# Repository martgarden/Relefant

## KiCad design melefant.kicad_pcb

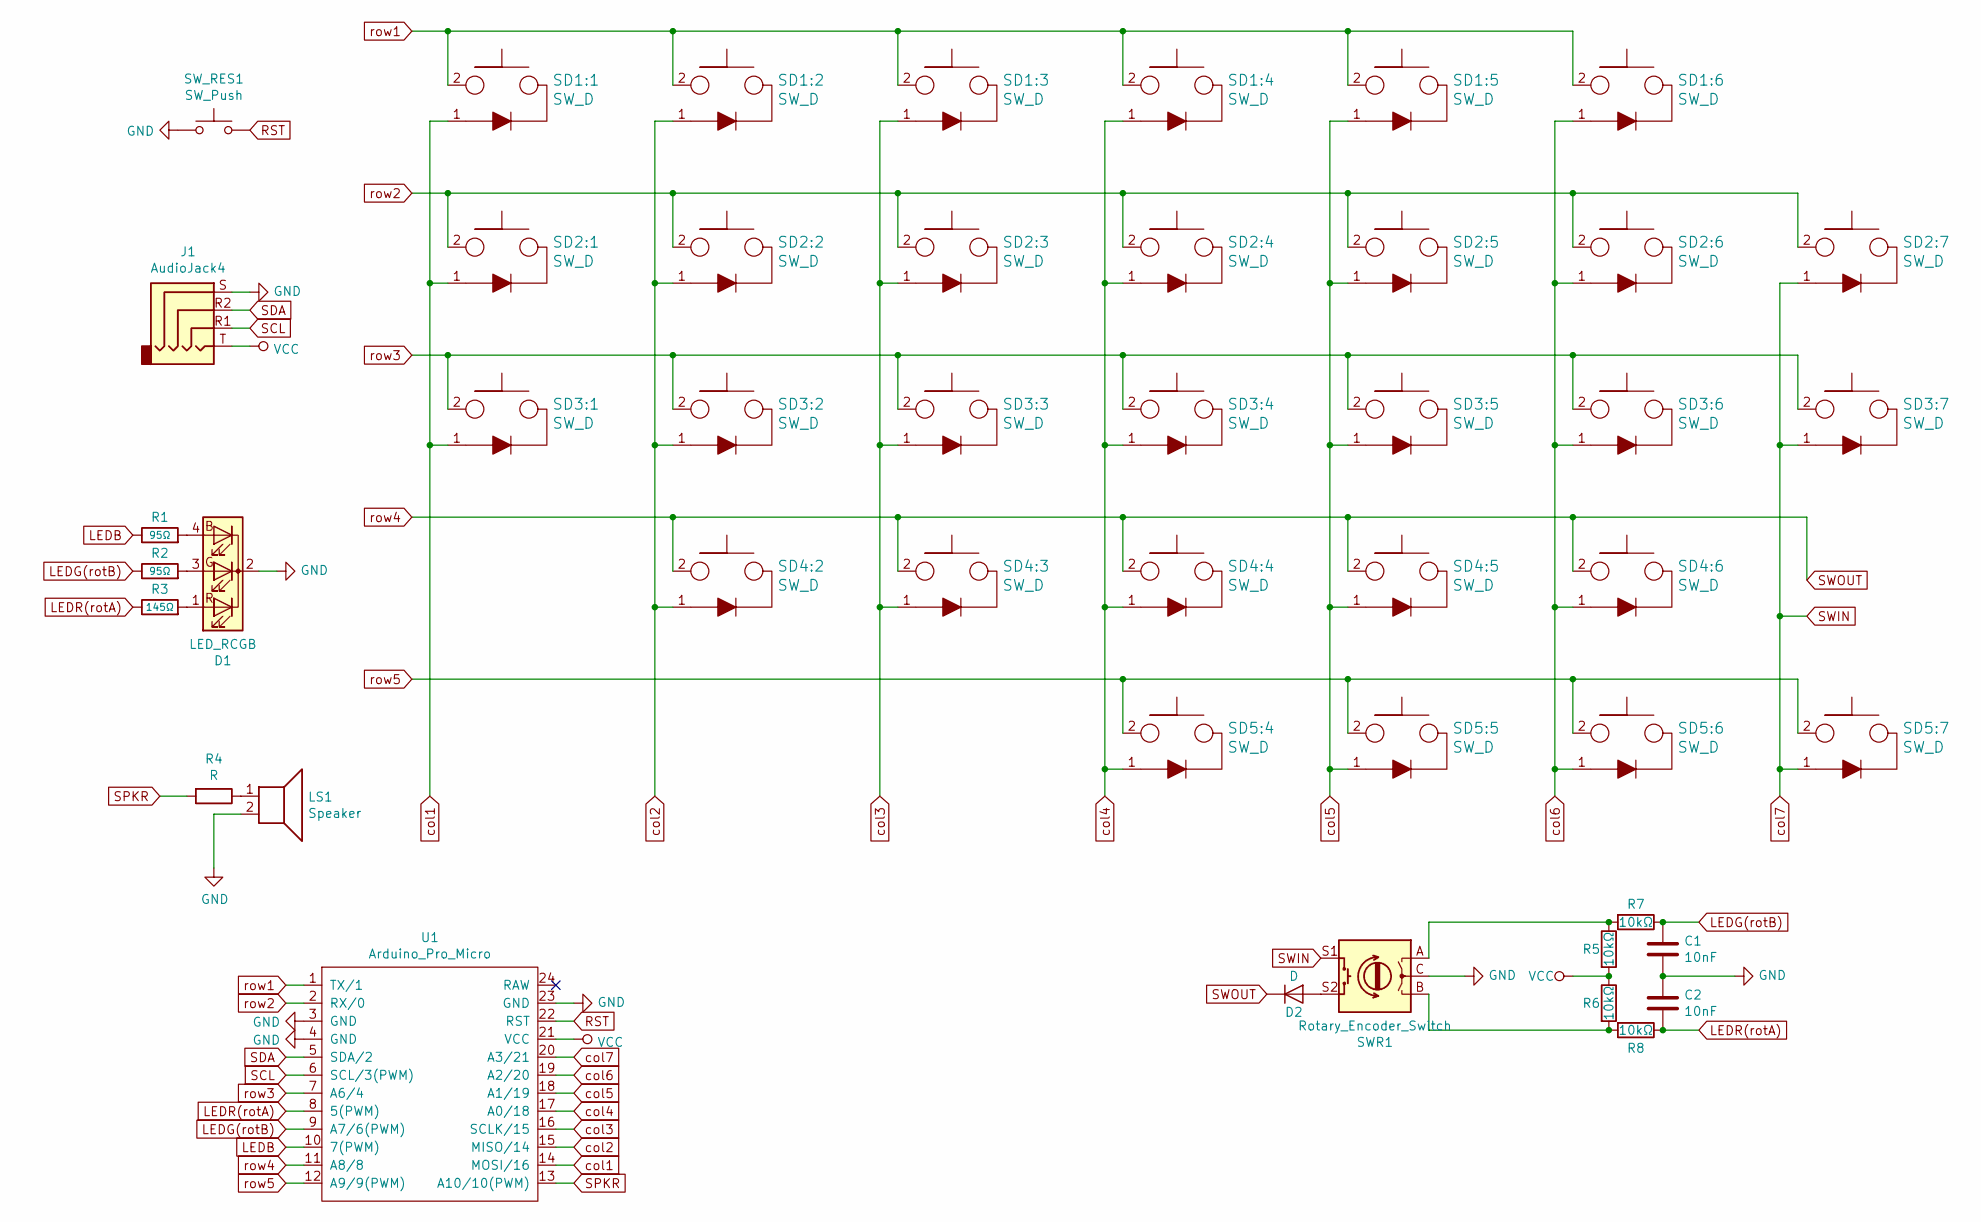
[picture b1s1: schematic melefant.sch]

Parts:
C1, C2: 10nF; C_Disc_D3.0mm_W2.0mm_P2.50mm
D1: LED_RCGB; LED_D5.0mm-4_RGB
D2: D; D_SOD123
J1: AudioJack4; TRRS-PJ320A-dbl
LS1: Speaker; PinHeader_1x02_P2.00mm_Vertical
R1, R2: 95Ω; R_Axial_DIN0207_L6.3mm_D2.5mm_P10.16mm_Horizontal
R3: 145Ω; R_Axial_DIN0207_L6.3mm_D2.5mm_P10.16mm_Horizontal
R4: R; R_Axial_DIN0207_L6.3mm_D2.5mm_P10.16mm_Horizontal
R5, R6, R7, R8: 10kΩ; R_Axial_DIN0207_L6.3mm_D2.5mm_P10.16mm_Horizontal
SD1:1, SD1:2, SD1:3, SD1:4, SD1:5, SD1:6, SD2:1, SD2:2, SD2:3, SD2:4, SD2:5, SD2:6, SD2:7, SD3:1, SD3:2, SD3:3, SD3:4, SD3:5, SD3:6, SD3:7, SD4:2, SD4:3, SD4:4, SD4:5, SD4:6, SD5:4, SD5:5, SD5:6, SD5:7: SW_D; cherry_mx_1u
SWR1: Rotary_Encoder_Switch; RotaryEncoder_Alps_EC11E-Switch_Vertical_H20mm
SW_RES1: SW_Push; SW_PUSH_6mm
U1: Arduino_Pro_Micro

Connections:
GND: C1.2, C2.1, D1.2 (K), J1.S, LS1.2, SWR1.C, SW_RES1.1, U1.3 (GND), U1.4 (GND), U1.23 (GND)
LEDB: R1.1, U1.10 (7(PWM))
LEDG(rotB): C1.1, R2.1, R7.1, U1.9 (A7/6(PWM))
LEDR(rotA): C2.2, R3.1, R8.1, U1.8 (5(PWM))
unnamed: D1.1 (RA), R3.2
unnamed: D1.3 (GA), R2.2
unnamed: D1.4 (BA), R1.2
unnamed: D2.2 (A), SWR1.S2
unnamed: LS1.1, R4.1
unnamed: R5.1, R7.2, SWR1.A
unnamed: R6.2, R8.2, SWR1.B
RST: SW_RES1.2, U1.22 (RST)
SCL: J1.R1, U1.6 (SCL/3(PWM))
SDA: J1.R2, U1.5 (SDA/2)
SPKR: R4.2, U1.13 (A10/10(PWM))
SWIN: SD2:7.1, SD3:7.1, SD5:7.1, SWR1.S1, U1.20 (A3/21)
SWOUT: D2.1 (K), SD4:2.2, SD4:3.2, SD4:4.2, SD4:5.2, SD4:6.2, U1.11 (A8/8)
VCC: J1.T, R5.2, R6.1, U1.21 (VCC)
col1: SD1:1.1, SD2:1.1, SD3:1.1, U1.14 (MOSI/16)
col2: SD1:2.1, SD2:2.1, SD3:2.1, SD4:2.1, U1.15 (MISO/14)
col3: SD1:3.1, SD2:3.1, SD3:3.1, SD4:3.1, U1.16 (SCLK/15)
col4: SD1:4.1, SD2:4.1, SD3:4.1, SD4:4.1, SD5:4.1, U1.17 (A0/18)
col5: SD1:5.1, SD2:5.1, SD3:5.1, SD4:5.1, SD5:5.1, U1.18 (A1/19)
col6: SD1:6.1, SD2:6.1, SD3:6.1, SD4:6.1, SD5:6.1, U1.19 (A2/20)
row1: SD1:1.2, SD1:2.2, SD1:3.2, SD1:4.2, SD1:5.2, SD1:6.2, U1.1 (TX/1)
row2: SD2:1.2, SD2:2.2, SD2:3.2, SD2:4.2, SD2:5.2, SD2:6.2, SD2:7.2, U1.2 (RX/0)
row3: SD3:1.2, SD3:2.2, SD3:3.2, SD3:4.2, SD3:5.2, SD3:6.2, SD3:7.2, U1.7 (A6/4)
row5: SD5:4.2, SD5:5.2, SD5:6.2, SD5:7.2, U1.12 (A9/9(PWM))

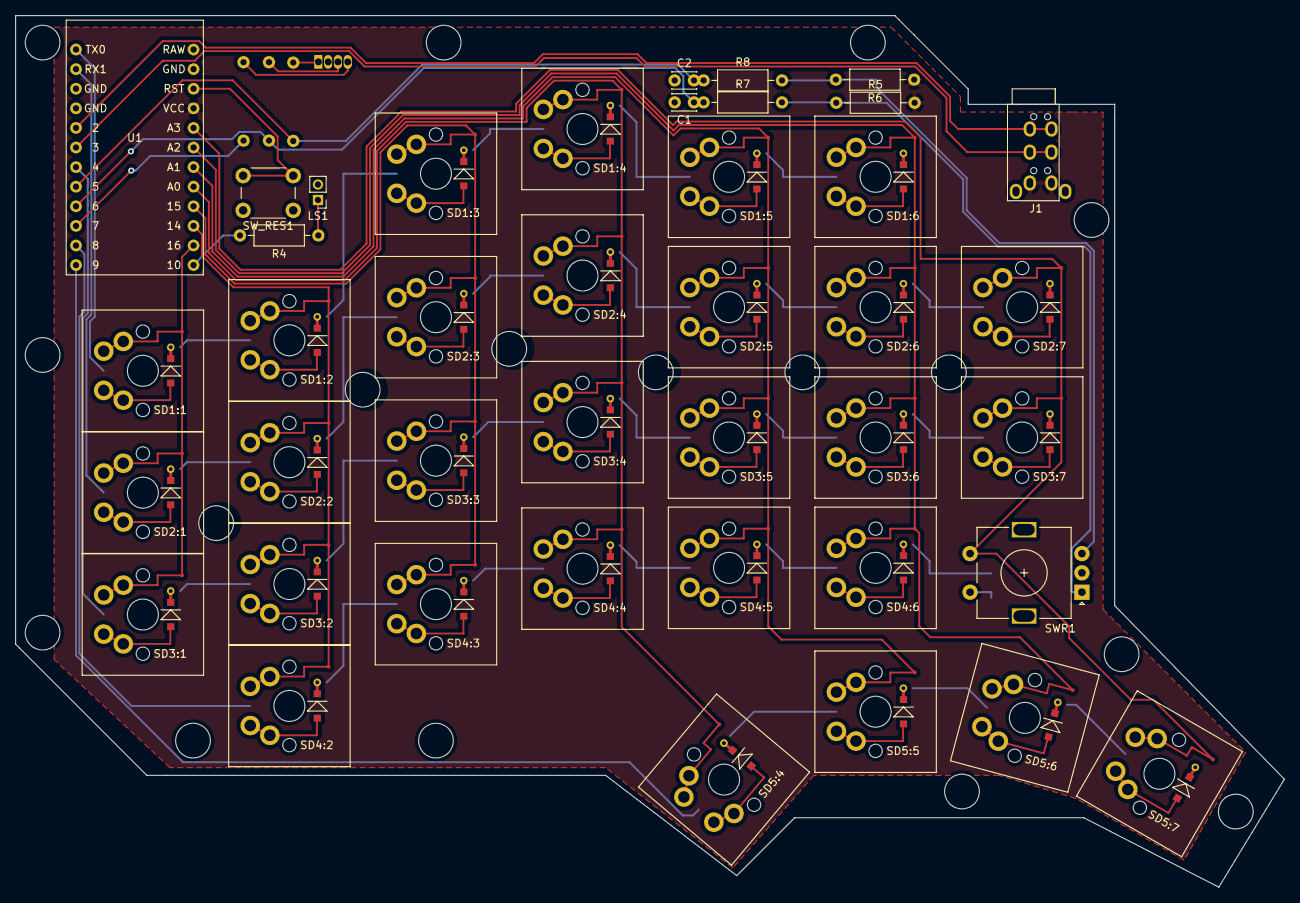
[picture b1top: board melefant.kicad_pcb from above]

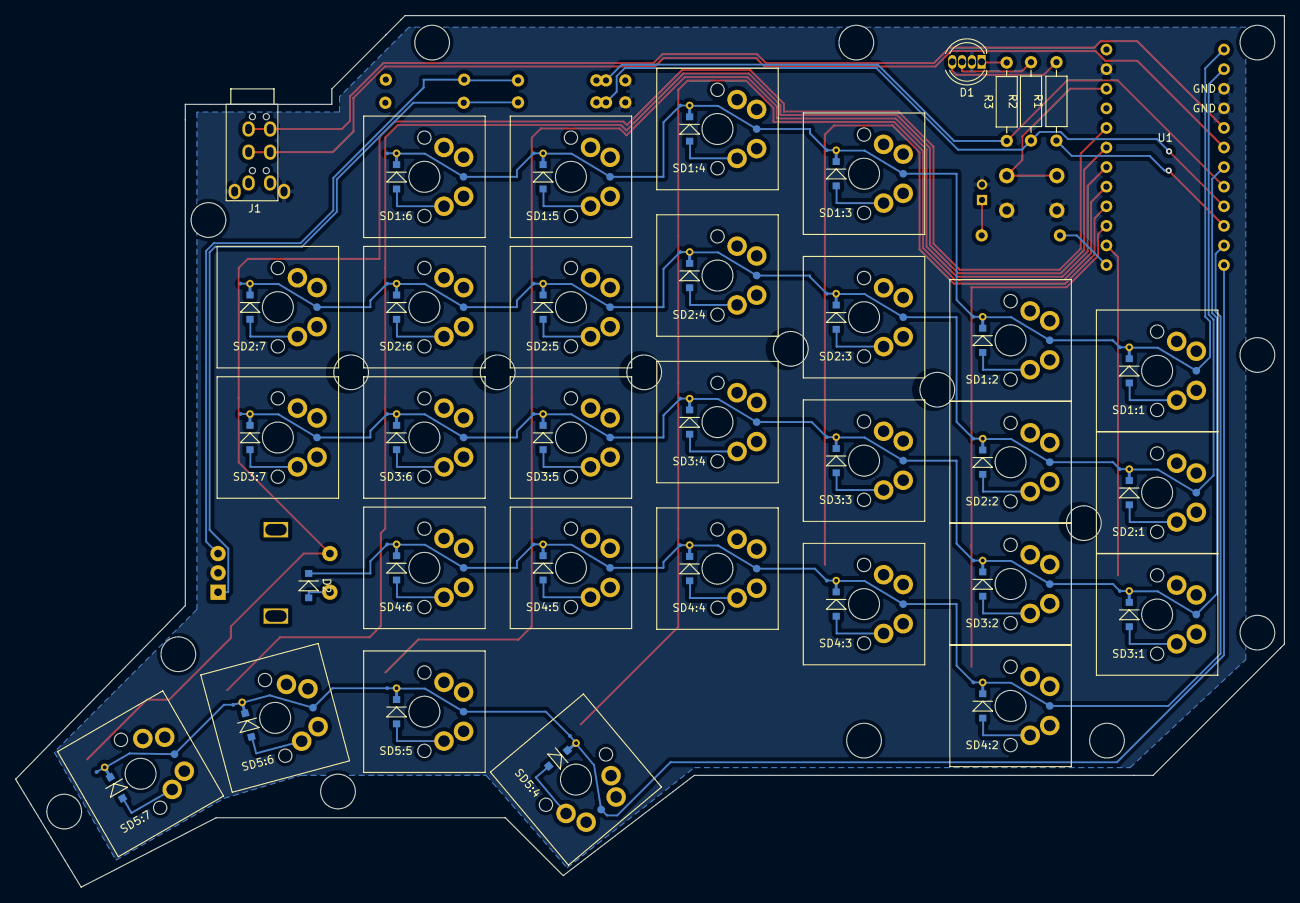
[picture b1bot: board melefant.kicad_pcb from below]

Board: 2 copper layers, 164.5 x 113.0 mm, 46 parts (5 on the bottom side), 28 nets.

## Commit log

2020-05-02 almost done
2020-05-03 pcb done.
2020-05-05 top plate
